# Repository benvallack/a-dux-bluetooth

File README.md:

# a-dux-bluetooth

Note: This needs further work, some routes aren’t connected properly. Please use for ideas only!

Simplified versions of [tapioki](https://github.com/tapioki)'s [Architeuthis dux](https://github.com/tapioki/cephalopoda/tree/main/Architeuthis%20dux) with puck and TRRS removed, cutout adjusted, power switch and reset switch added. Desiged for wireless use with nice!nanos.

Board is reversable so controlles facedown on left and face up on the right. The power switch and reset switch should work on both sides too. 

CURRENTLY UNTESTED!

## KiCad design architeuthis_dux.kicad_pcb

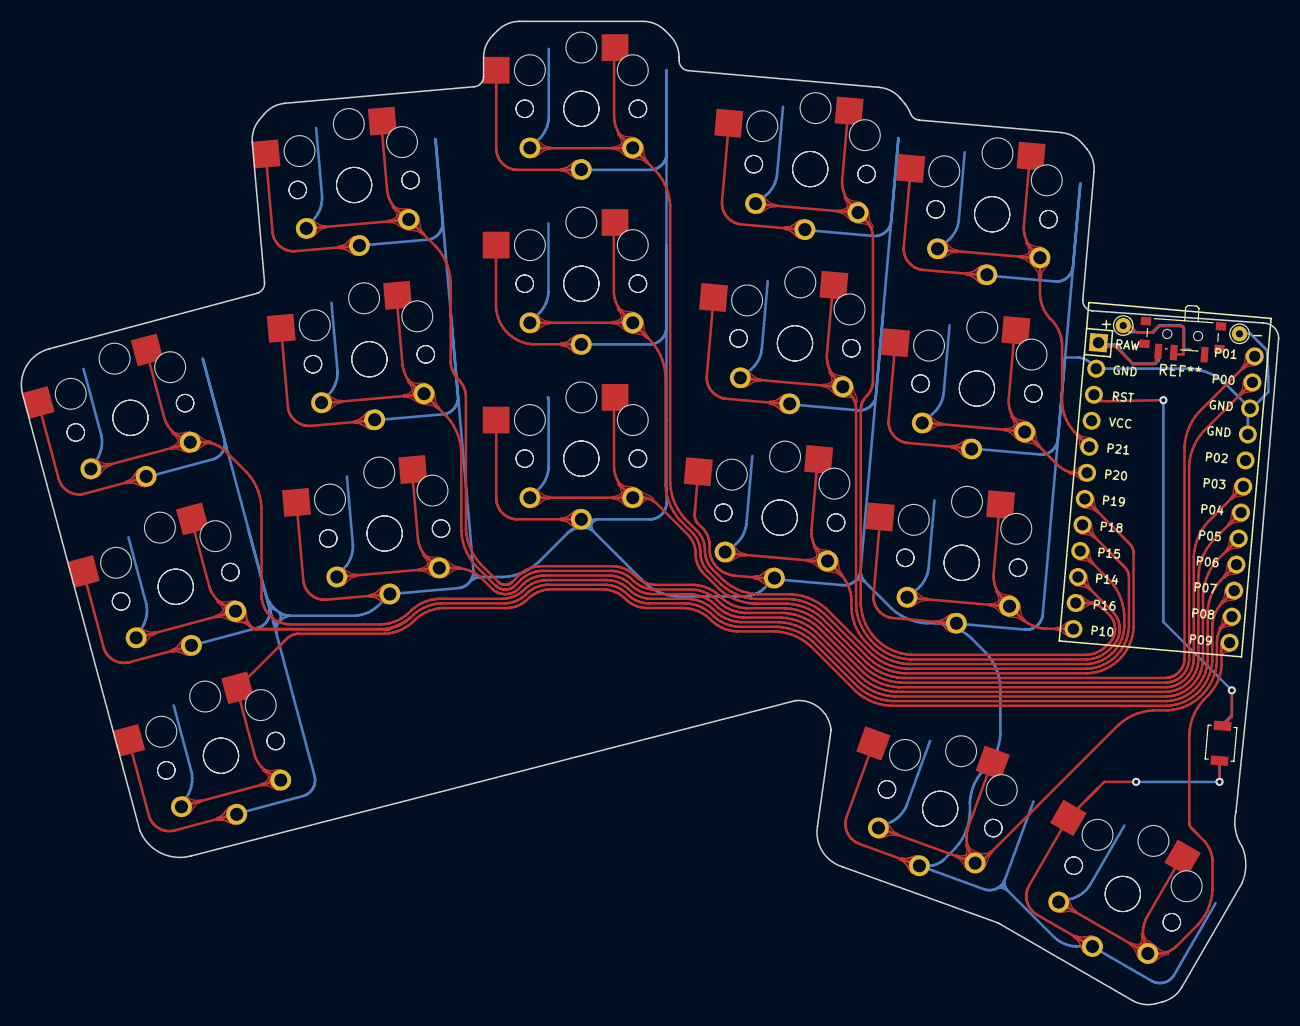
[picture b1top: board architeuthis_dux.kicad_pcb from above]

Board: 2 copper layers, 122.2 x 95.6 mm, 39 parts (1 on the bottom side), 18 nets.

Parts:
 : SW_SPST_B3U-1000P
 #2: SW_SPST_B3U-1000P
+: TestPoint_THTPad_D1.5mm_Drill0.7mm
-: TestPoint_THTPad_D1.5mm_Drill0.7mm
C1: ProMicro
S1, S2, S3, S4, S5, S6, S7, S8, S9, S10, S11, S12, S13, S14, S15, S16, S17, S18, S19, S20, S21, S22, S23, S24, S25, S26, S27, S28, S29, S30, S31, S32, S33, S34: PG1350

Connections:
GND: C1.2, C1.15, C1.16, S1.2, S2.2, S3.2, S4.2, S5.2, S6.2, S7.2, S8.2, S9.2, S10.2, S11.2, S12.2, S13.2, S14.2, S15.2, S16.2, S17.2, S18.2, S19.2, S20.2, S21.2, S22.2, S23.2, S24.2, S25.2, S26.2, S27.2, S28.2, S29.2, S30.2, S31.2, S32.2, S33.2, S34.2
P0: C1.14, S11.1, S12.1
P1: C1.13, S13.1, S14.1
P3: C1.18, S9.1, S10.1
P4: C1.19, S7.1, S8.1
P5: C1.20, S5.1, S6.1
P6: C1.21, S3.1, S4.1
P7: C1.22, S1.1, S2.1
P8: C1.23, S31.1, S32.1
P9: C1.24, S33.1, S34.1
P10: C1.12, S25.1, S26.1
P14: C1.10, S21.1, S22.1
P15: C1.9, S19.1, S20.1
P16: C1.11, S23.1, S24.1
P18: C1.8, S17.1, S18.1
P19: C1.7, S15.1, S16.1
P20: C1.6, S27.1, S28.1
P21: C1.5, S29.1, S30.1

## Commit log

2021-10-09 files
2021-10-09 remove bad route
2021-10-09 gerber
